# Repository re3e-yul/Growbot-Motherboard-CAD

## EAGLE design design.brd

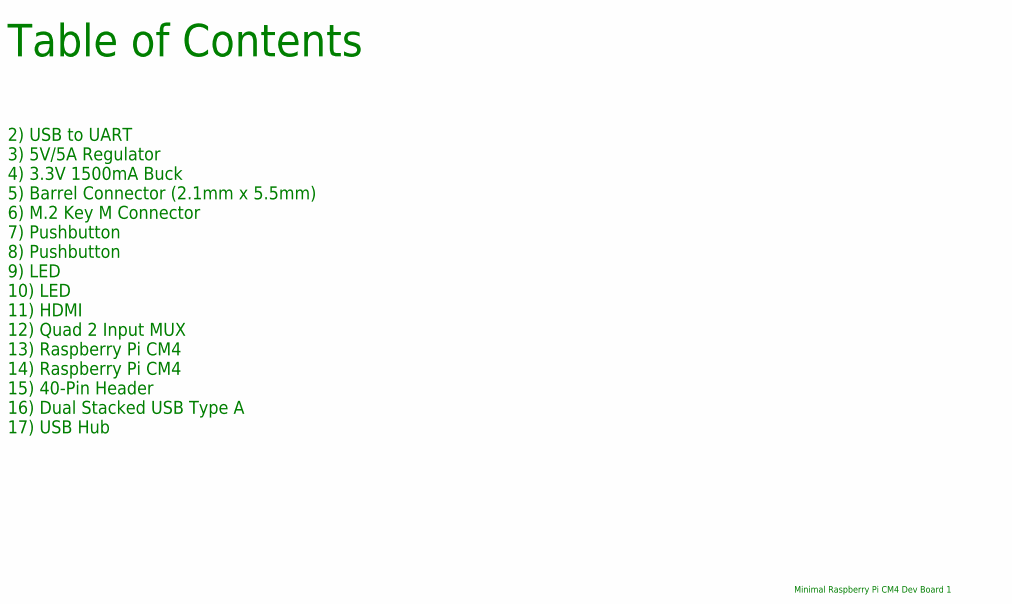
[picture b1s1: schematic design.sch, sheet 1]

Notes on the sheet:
Table of Contents
Minimal Raspberry Pi CM4 Dev Board 1
2) USB to UART
3) 5V/5A Regulator
4) 3.3V 1500mA Buck
5) Barrel Connector (2.1mm x 5.5mm)
6) M.2 Key M Connector
7) Pushbutton
8) Pushbutton
9) LED
10) LED
11) HDMI
12) Quad 2 Input MUX
13) Raspberry Pi CM4
14) Raspberry Pi CM4
15) 40-Pin Header
16) Dual Stacked USB Type A
17) USB Hub

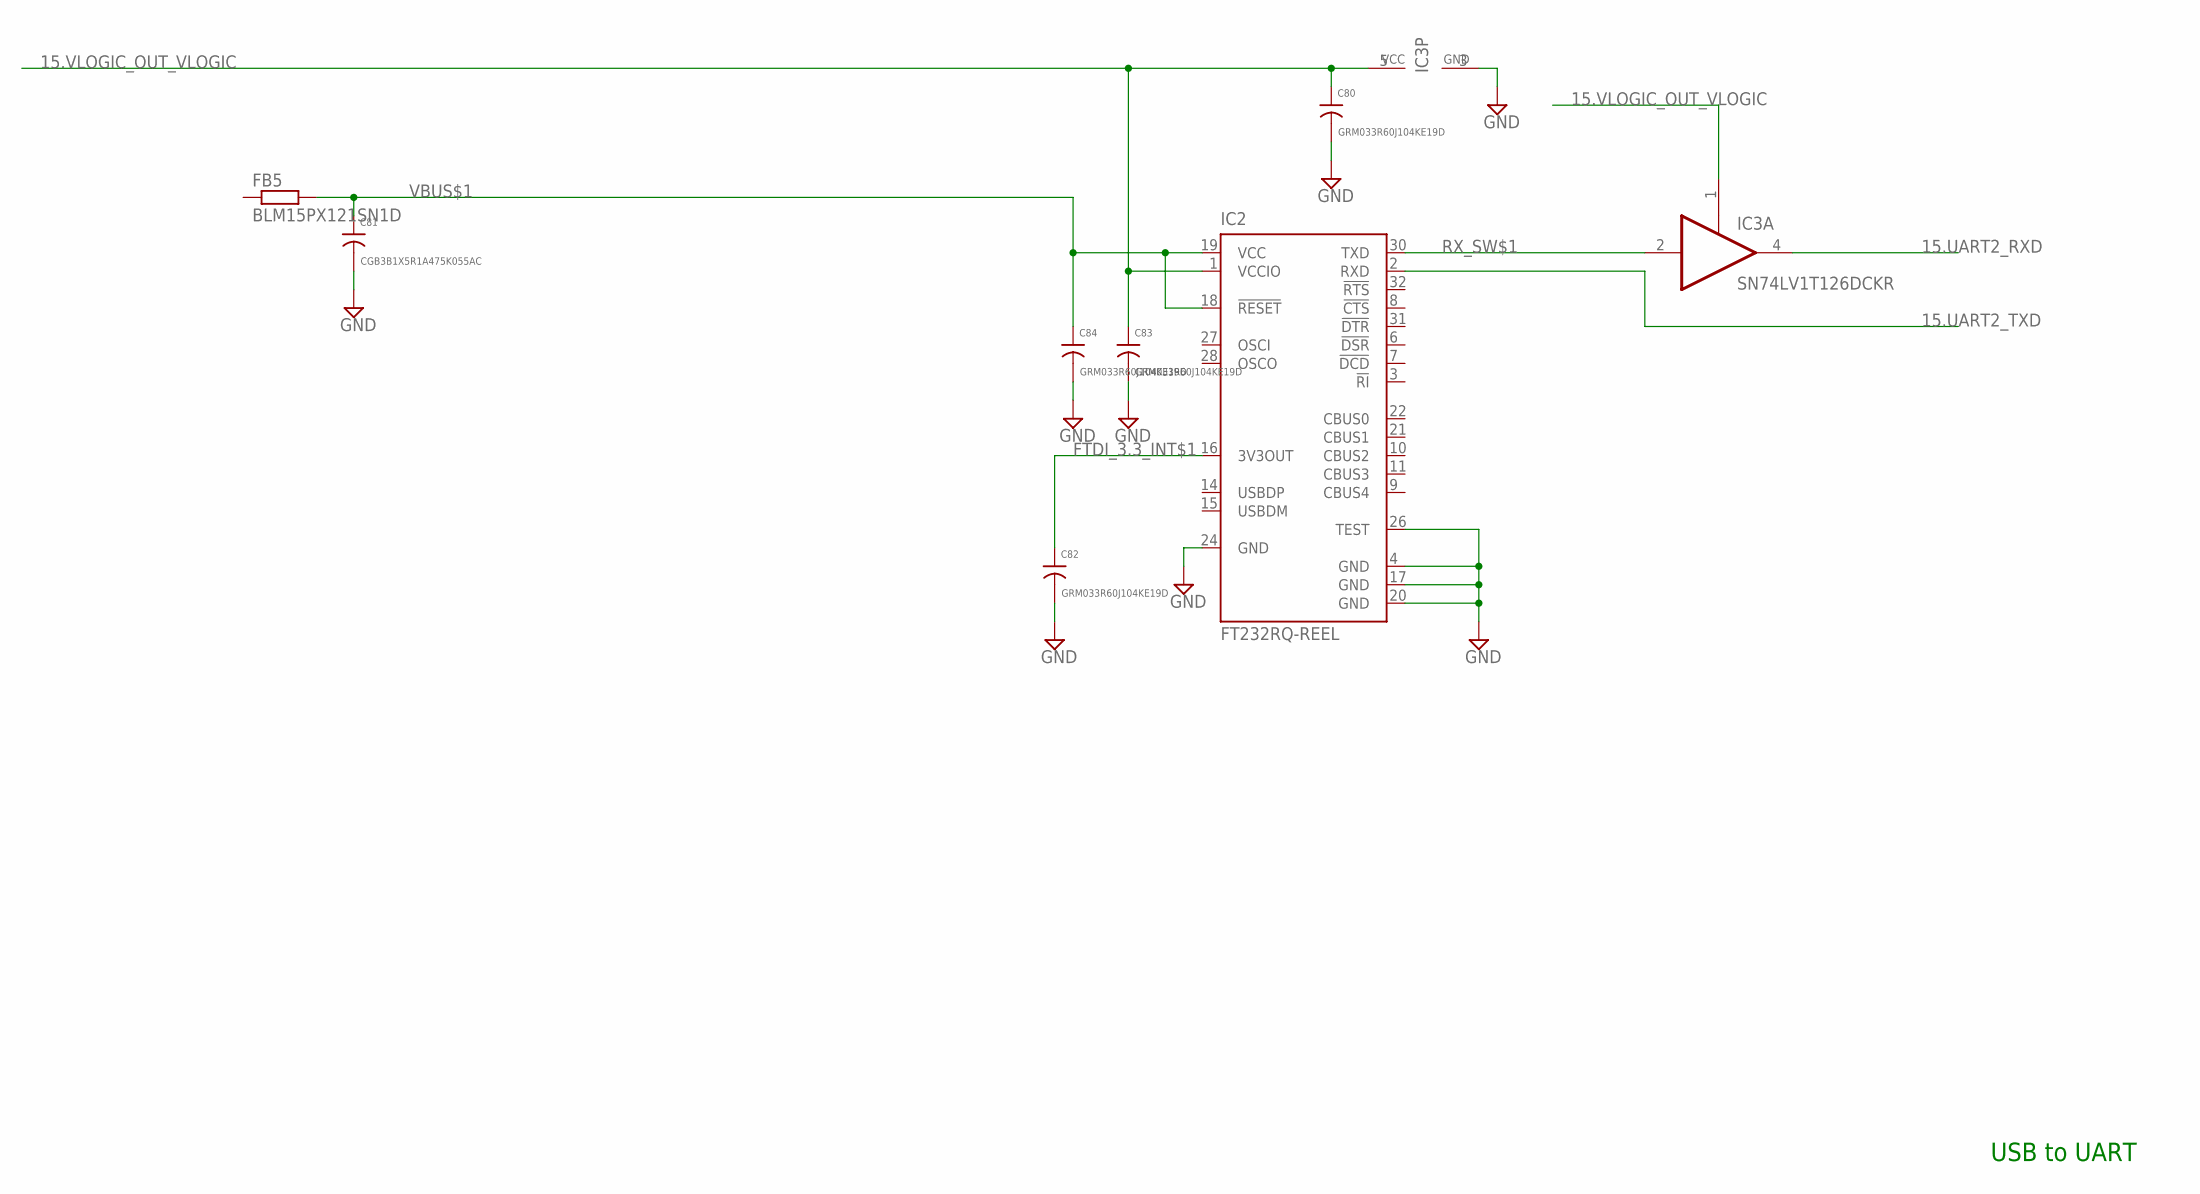
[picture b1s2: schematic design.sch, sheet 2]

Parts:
C80, C82, C83, C84: GRM033R60J104KE19D; 0201
C81: CGB3B1X5R1A475K055AC; 0603
FB5: BLM15PX121SN1D; 0402
IC2: FT232RQ-REEL; QFN32
IC3: SN74LV1T126DCKR; SC70-5

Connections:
15.UART2_RXD: IC3.4 (O); also elsewhere on the board
15.UART2_TXD: IC2.2 (RXD); also elsewhere on the board
15.VLOGIC_OUT_VLOGIC: C80.1, C83.1, IC2.1 (VCCIO), IC3.1 (OE), IC3.5 (VCC); also elsewhere on the board
FTDI_3.3_INT$1: C82.1, IC2.16 (3V3OUT)
GND: C80.2, C81.2, C82.2, C83.2, C84.2, IC2.4 (GND), IC2.17 (GND), IC2.20 (GND), IC2.24 (GND), IC2.26 (TEST), IC3.3 (GND); also elsewhere on the board
RX_SW$1: IC2.30 (TXD), IC3.2 (I)
VBUS$1: C81.1, C84.1, FB5.2, IC2.18 (!RESET), IC2.19 (VCC)

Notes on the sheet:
USB to UART

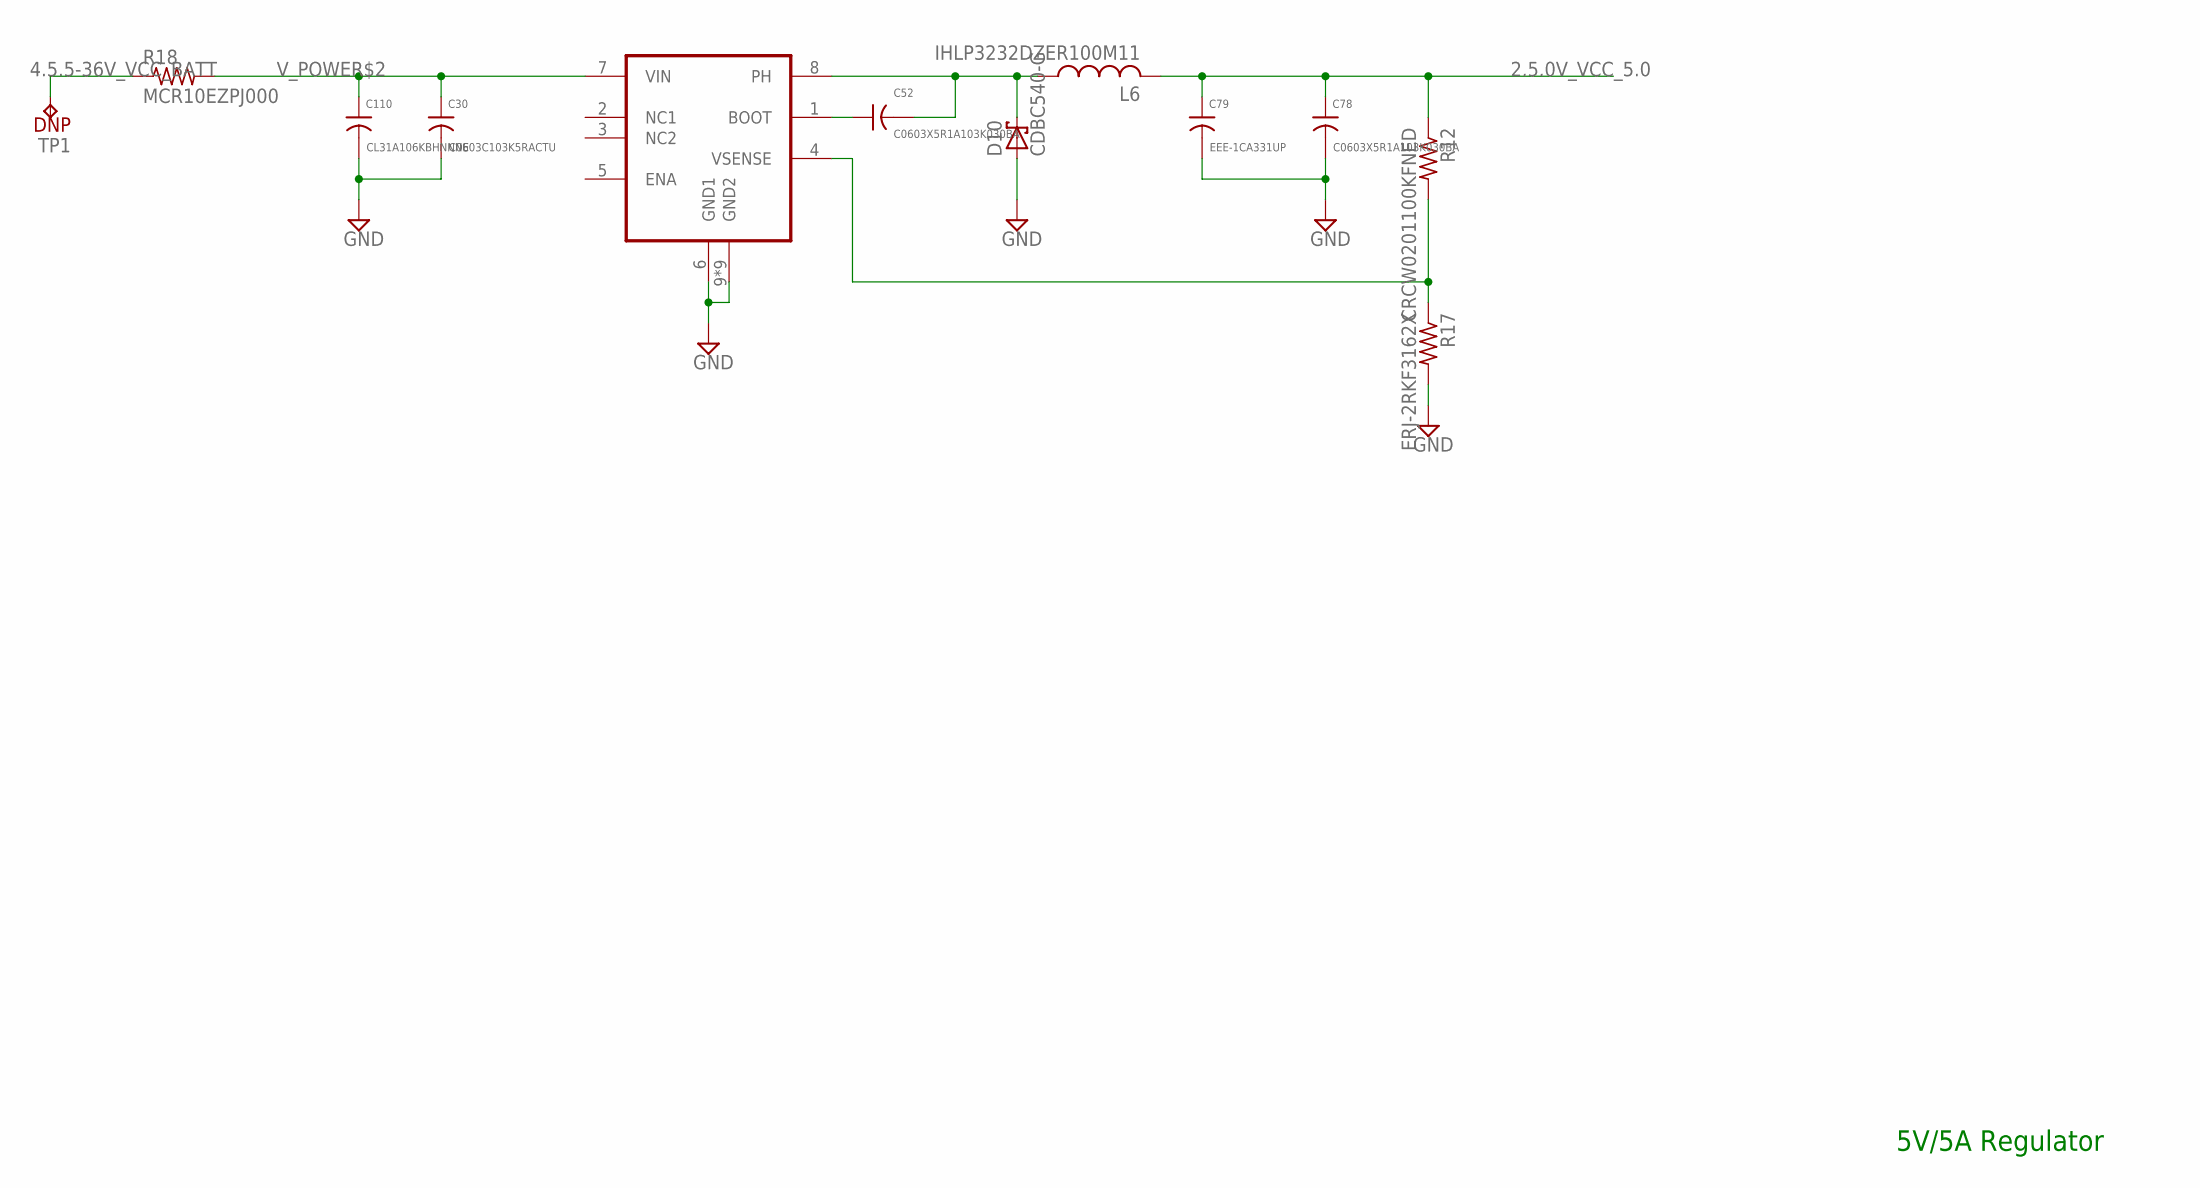
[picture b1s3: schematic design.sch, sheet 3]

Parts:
C30: C0603C103K5RACTU; 0603
C52, C78: C0603X5R1A103K030BA; 0201
C79: EEE-1CA331UP; PANASONIC_F
C110: CL31A106KBHNNNE; 1206
D10: CDBC540-G; DO-214AB
L6: IHLP3232DZER100M11; 3232DZ
R12: CRCW0201100KFNED; 0201
R17: ERJ-2RKF3162X; 0402
R18: MCR10EZPJ000; 0805
TP1: DNP; TP0500
U6: TPS5450QDDARQ1; 8SO_POWERPAD

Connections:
2.5.0V_VCC_5.0: C78.1, C79.+ (1), L6.2, R12.1; also elsewhere on the board
4.5.5-36V_VCC_BATT: R18.1, TP1.1; also elsewhere on the board
BOOT$2: C52.1, U6.1 (BOOT)
GND: C30.2, C78.2, C79.- (2), C110.2, D10.A, R17.2, U6.6 (GND1), U6.9 (GND2), U6.PWRPAD1 (GND2), U6.PWRPAD2 (GND2), U6.PWRPAD3 (GND2), U6.PWRPAD4 (GND2), U6.PWRPAD5 (GND2), U6.PWRPAD6 (GND2), U6.PWRPAD7 (GND2), U6.PWRPAD8 (GND2); also elsewhere on the board
PH$2: C52.2, D10.C, L6.1, U6.8 (PH)
VSENSE$2: R12.2, R17.1, U6.4 (VSENSE)
V_POWER$2: C30.1, C110.1, R18.2, U6.7 (VIN)

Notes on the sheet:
5V/5A Regulator

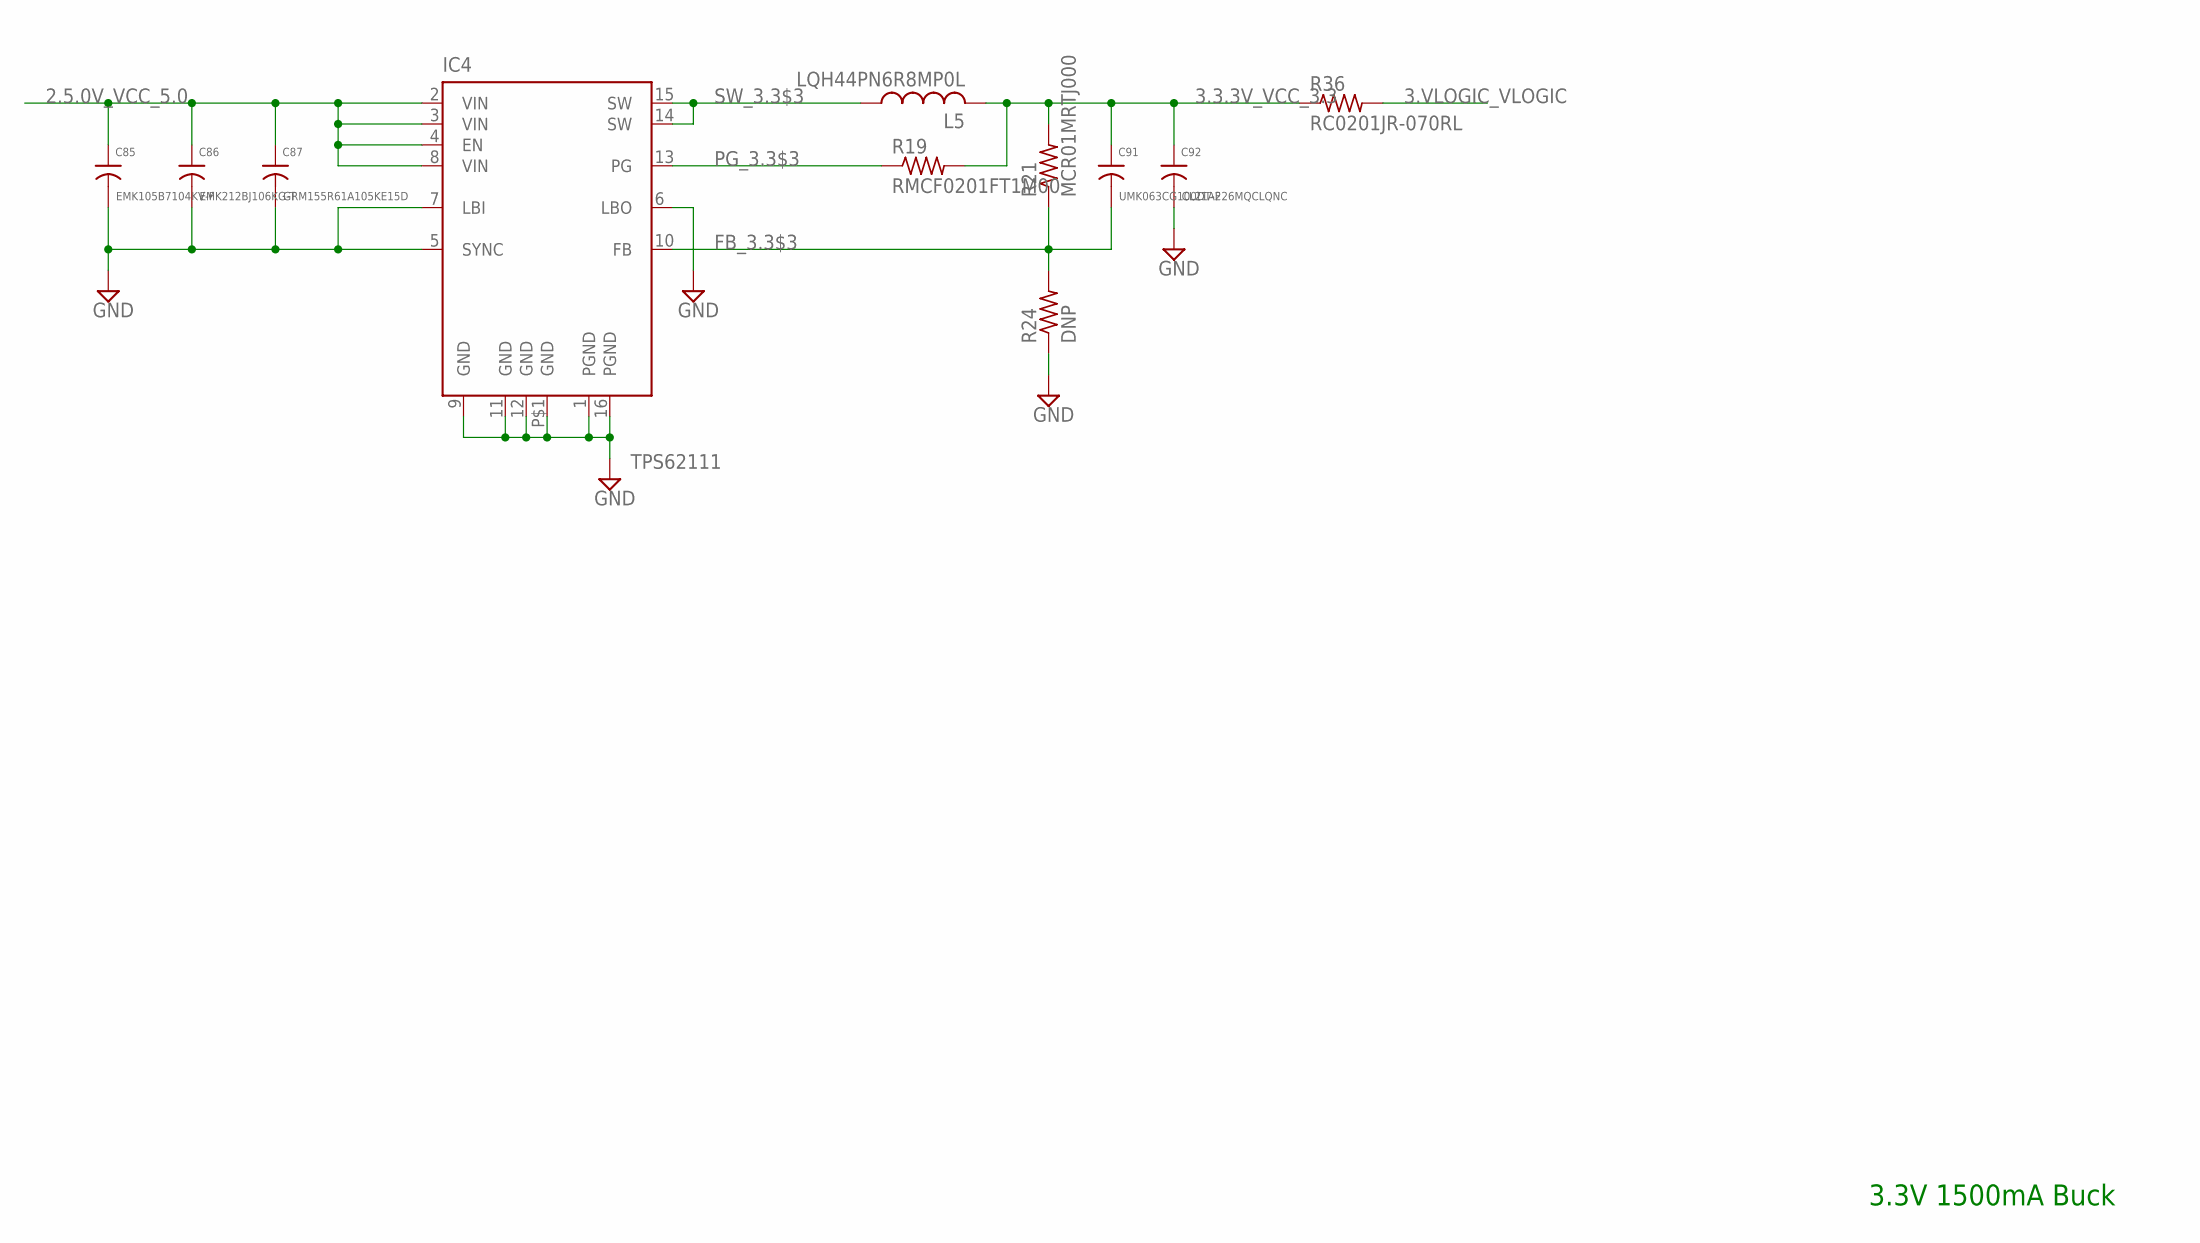
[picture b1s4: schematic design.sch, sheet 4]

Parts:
C85: EMK105B7104KV-F; 0402
C86: EMK212BJ106KG-T; 0805
C87: GRM155R61A105KE15D; 0402
C91: UMK063CG100DT-F; 0201
C92: CL21A226MQCLQNC; 0805
IC4: TPS62111; PQFP16
L5: LQH44PN6R8MP0L; 1515
R19: RMCF0201FT1M00; 0201
R21: MCR01MRTJ000; 0402
R24: DNP; 0402
R36: RC0201JR-070RL; 0201

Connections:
2.5.0V_VCC_5.0: C85.1, C86.1, C87.1, IC4.2 (VIN), IC4.3 (VIN), IC4.4 (EN), IC4.8 (VIN); also elsewhere on the board
3.3.3V_VCC_3.3: C91.1, C92.1, L5.2, R19.2, R21.2, R36.1; also elsewhere on the board
3.VLOGIC_VLOGIC: R36.2
FB_3.3$3: C91.2, IC4.10 (FB), R21.1, R24.2
GND: C85.2, C86.2, C87.2, C92.2, IC4.1 (PGND), IC4.5 (SYNC), IC4.6 (LBO), IC4.7 (LBI), IC4.9 (GND), IC4.11 (GND), IC4.12 (GND), IC4.16 (PGND), IC4.P$1 (GND), R24.1; also elsewhere on the board
PG_3.3$3: IC4.13 (PG), R19.1
SW_3.3$3: IC4.14 (SW), IC4.15 (SW), L5.1

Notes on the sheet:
3.3V 1500mA Buck

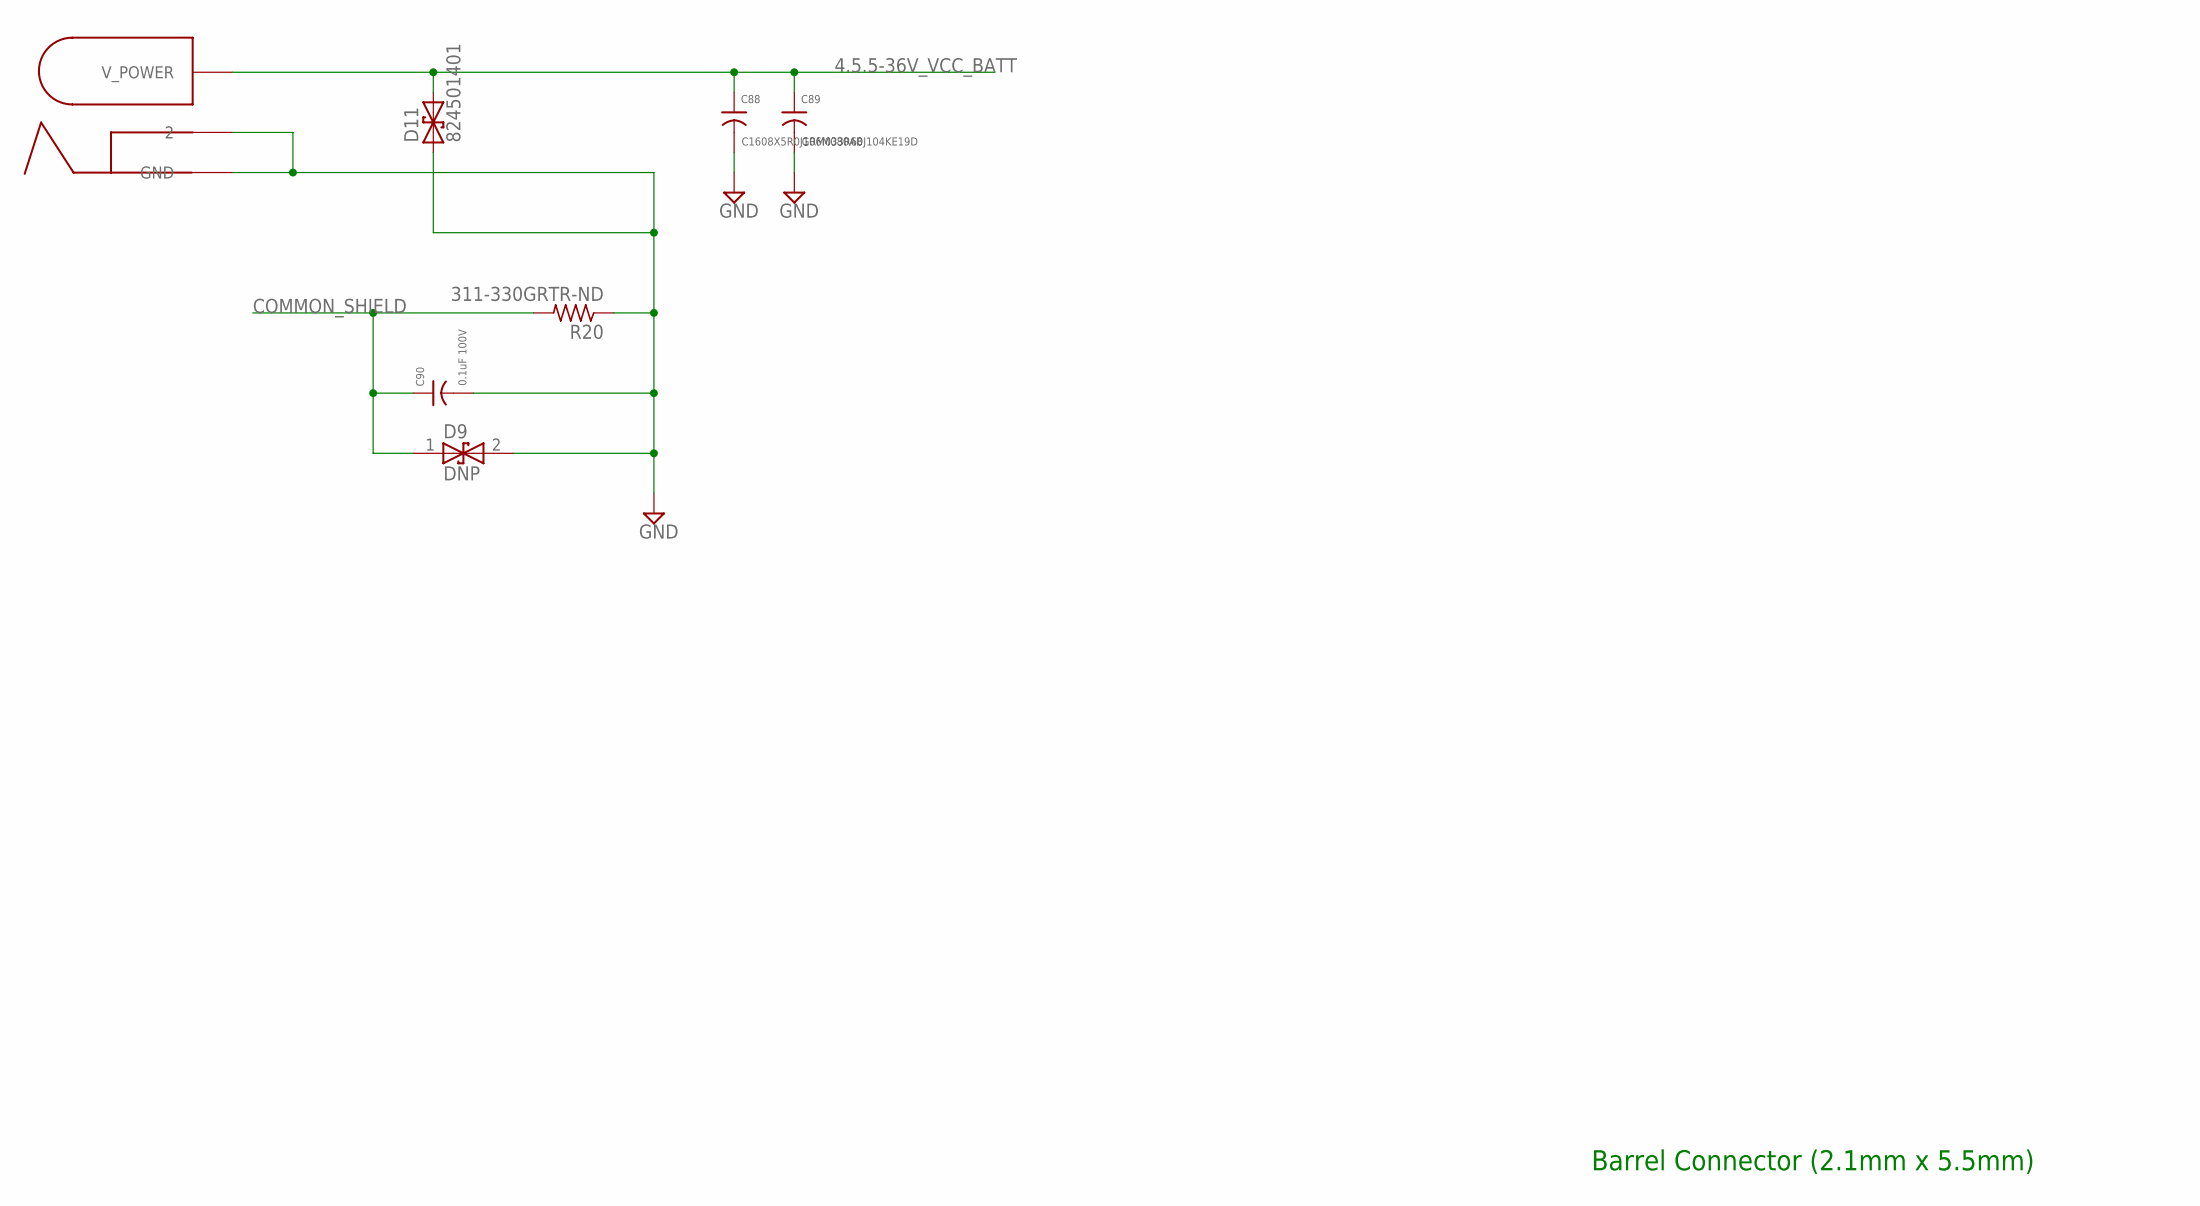
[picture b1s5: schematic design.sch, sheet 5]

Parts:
C88: C1608X5R0J106M080AB; 0603
C89: GRM033R60J104KE19D; 0201
C90: 0.1uF 100V; 1206
D9: DNP; TPD1E
D11: 824501401; SMAJ
J3: PJ-002AH; PJ-002A
R20: 311-330GRTR-ND; 0603

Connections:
4.5.5-36V_VCC_BATT: C88.1, C89.1, D11.C (2), J3.1 (V_POWER); also elsewhere on the board
COMMON_SHIELD: C90.1, D9.1, R20.2; also elsewhere on the board
GND: C88.2, C89.2, C90.2, D9.2, D11.A (1), J3.2 (GND), J3.3 (2), R20.1; also elsewhere on the board

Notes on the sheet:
Barrel Connector (2.1mm x 5.5mm)

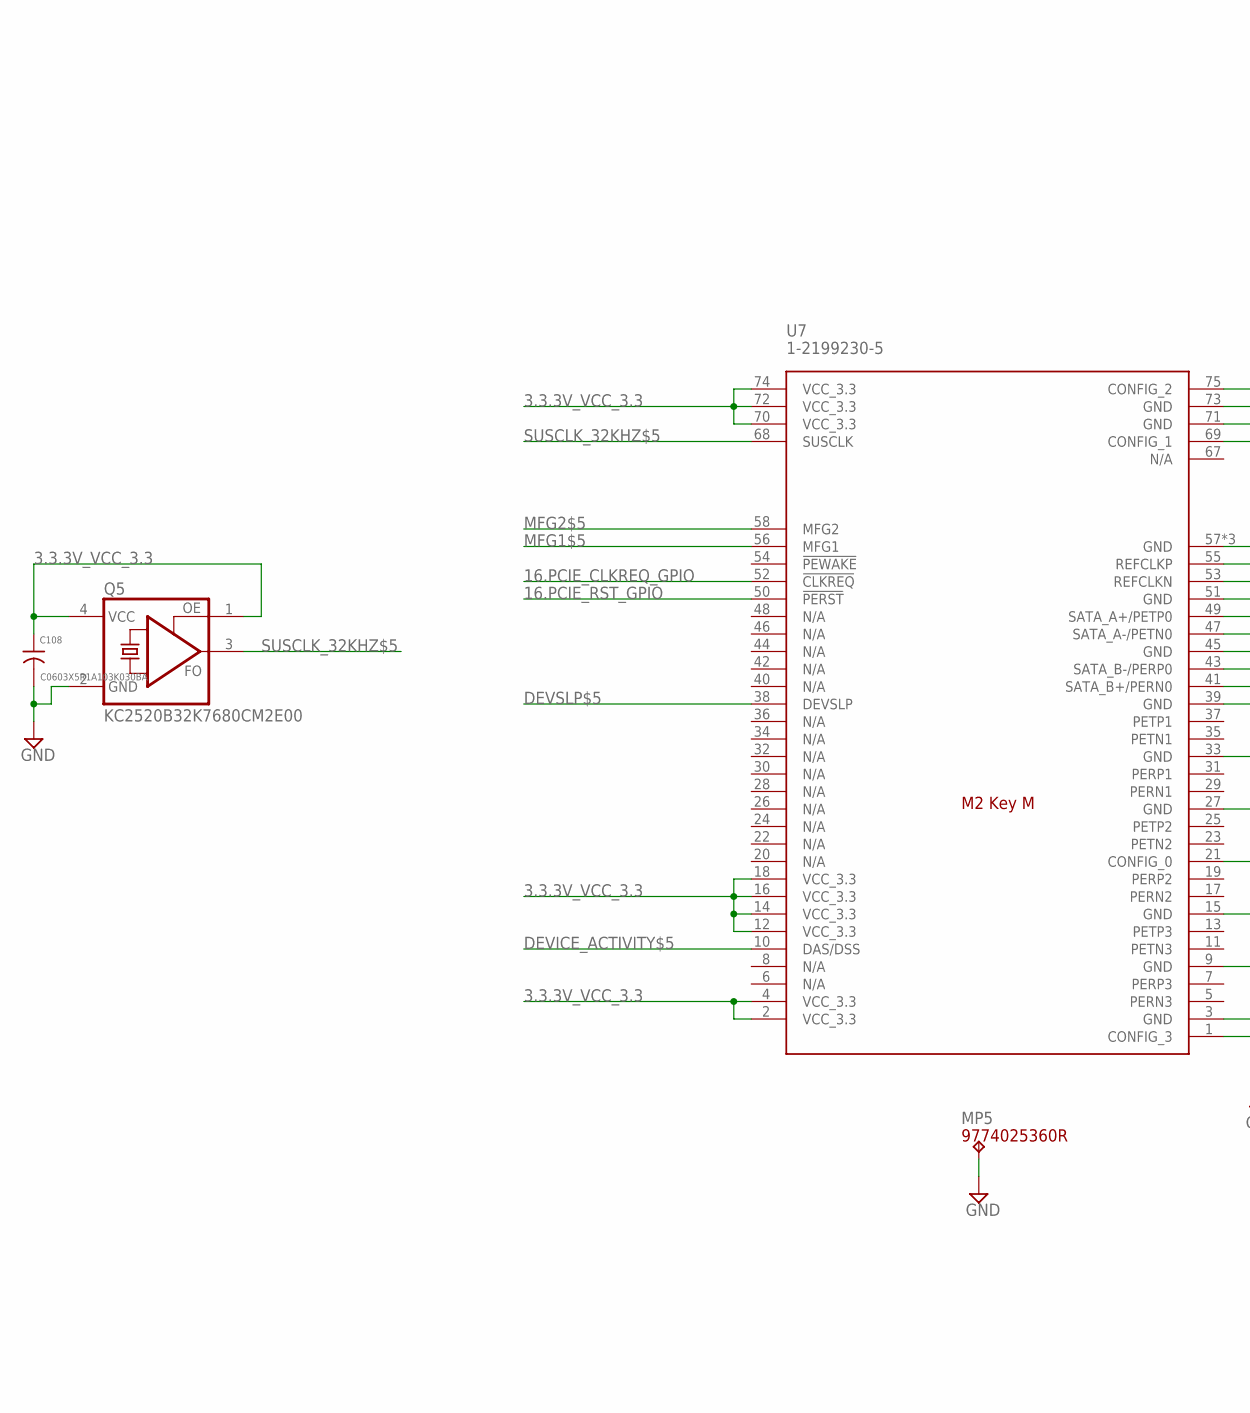
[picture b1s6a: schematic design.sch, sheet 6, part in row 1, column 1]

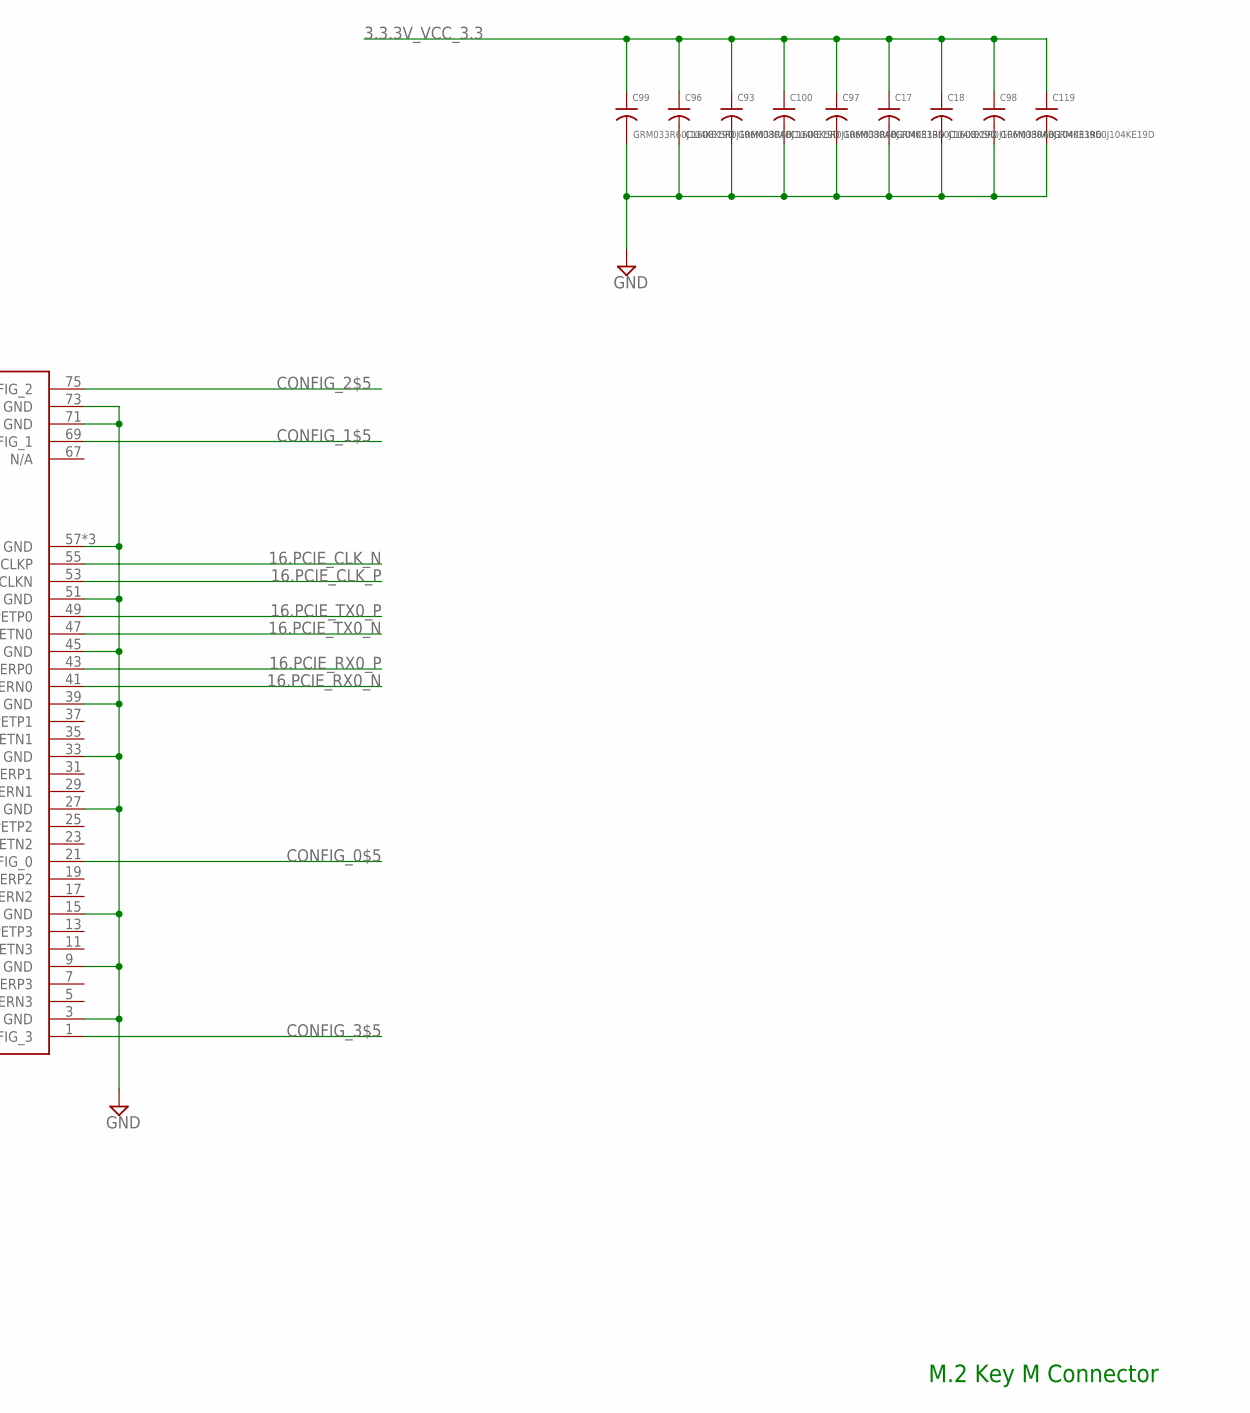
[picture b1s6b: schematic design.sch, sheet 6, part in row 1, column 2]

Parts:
C17, C93, C97, C98, C99, C119: GRM033R60J104KE19D; 0201
C18, C96, C100: C1608X5R0J106M080AB; 0603
C108: C0603X5R1A103K030BA; 0201
MP5: 9774025360R; WA-SMSI_9774___360
Q5: KC2520B32K7680CM2E00; VLGA-4
U7: 1-2199230-5; 2199230_KEY_M

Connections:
3.3.3V_VCC_3.3: C17.1, C18.1, C93.1, C96.1, C97.1, C98.1, C99.1, C100.1, C108.1, C119.1, Q5.1 (OE), Q5.4 (VCC), U7.2 (VCC_3.3), U7.4 (VCC_3.3), U7.12 (VCC_3.3), U7.14 (VCC_3.3), U7.16 (VCC_3.3), U7.18 (VCC_3.3), U7.70 (VCC_3.3), U7.72 (VCC_3.3), U7.74 (VCC_3.3); also elsewhere on the board
16.PCIE_CLKREQ_GPIO: U7.52 (!CLKREQ); also elsewhere on the board
16.PCIE_CLK_N: U7.55 (REFCLKP); also elsewhere on the board
16.PCIE_CLK_P: U7.53 (REFCLKN); also elsewhere on the board
16.PCIE_RST_GPIO: U7.50 (!PERST); also elsewhere on the board
16.PCIE_RX0_N: U7.41 (SATA_B+/PERN0); also elsewhere on the board
16.PCIE_RX0_P: U7.43 (SATA_B-/PERP0); also elsewhere on the board
16.PCIE_TX0_N: U7.47 (SATA_A-/PETN0); also elsewhere on the board
16.PCIE_TX0_P: U7.49 (SATA_A+/PETP0); also elsewhere on the board
CONFIG_0$5: U7.21 (CONFIG_0)
CONFIG_1$5: U7.69 (CONFIG_1)
CONFIG_2$5: U7.75 (CONFIG_2)
CONFIG_3$5: U7.1 (CONFIG_3)
DEVICE_ACTIVITY$5: U7.10 (DAS/DSS)
DEVSLP$5: U7.38 (DEVSLP)
GND: C17.2, C18.2, C93.2, C96.2, C97.2, C98.2, C99.2, C100.2, C108.2, C119.2, MP5.1, Q5.2 (GND), U7.3 (GND), U7.9 (GND), U7.15 (GND), U7.27 (GND), U7.33 (GND), U7.39 (GND), U7.45 (GND), U7.51 (GND), U7.57 (GND), U7.71 (GND), U7.73 (GND), U7.P$1 (GND), U7.P$2 (GND); also elsewhere on the board
MFG1$5: U7.56 (MFG1)
MFG2$5: U7.58 (MFG2)
SUSCLK_32KHZ$5: Q5.3 (FO), U7.68 (SUSCLK)

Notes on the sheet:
M.2 Key M Connector

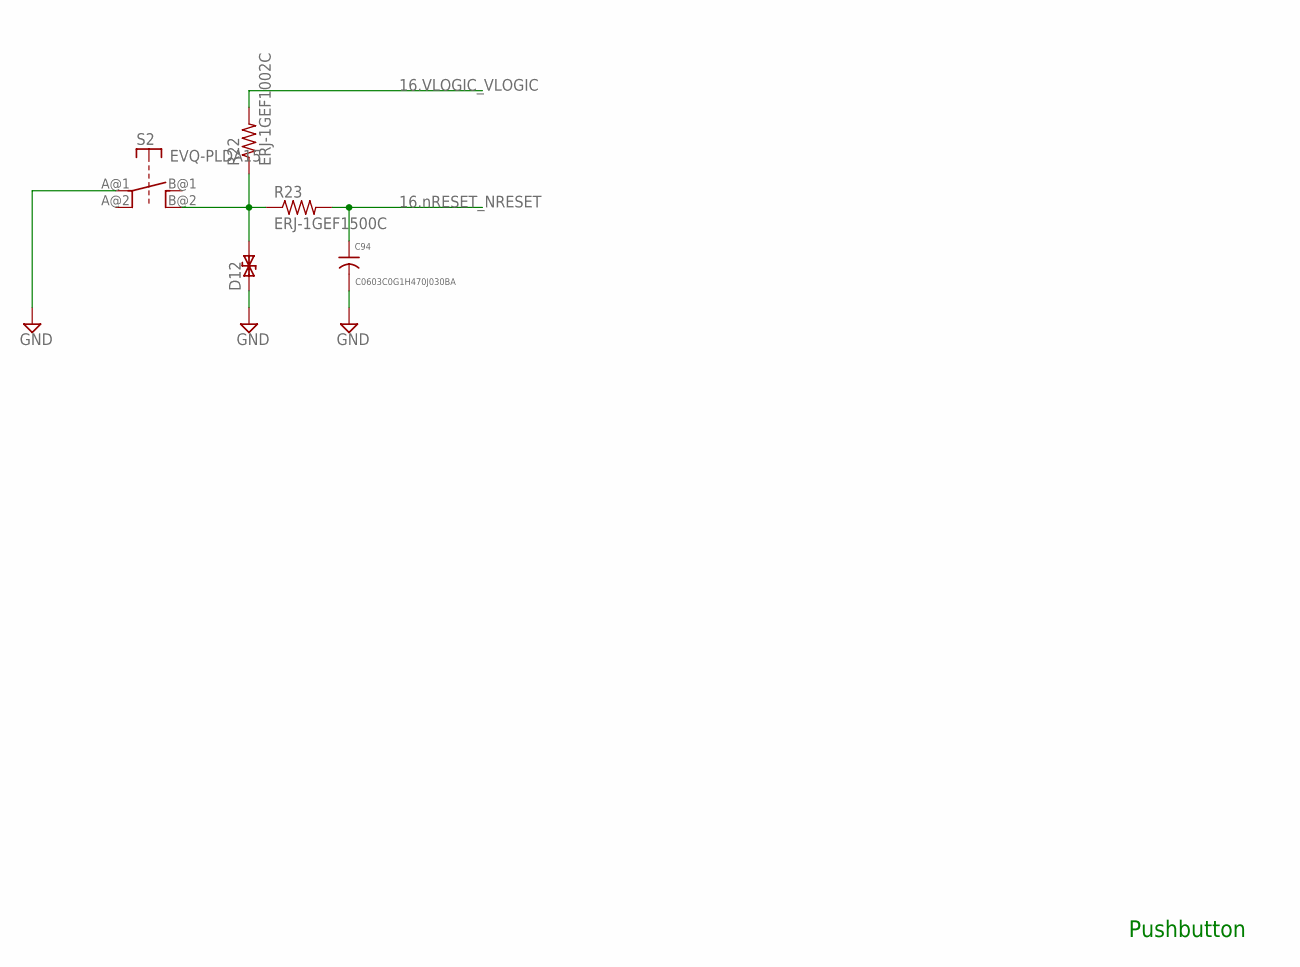
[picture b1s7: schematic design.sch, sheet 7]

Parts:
C94: C0603C0G1H470J030BA; 0201
D12: B72590D0050A060; D0402
R22: ERJ-1GEF1002C; 0201
R23: ERJ-1GEF1500C; 0201
S2: EVQ-PLDA15; EVQ

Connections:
16.VLOGIC_VLOGIC: R22.2; also elsewhere on the board
16.nRESET_NRESET: C94.1, R23.2; also elsewhere on the board
BTN_A$10: D12.P2, R22.1, R23.1, S2.B@2 (B')
GND: C94.2, D12.P1, S2.A@1 (A); also elsewhere on the board

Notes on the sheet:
Pushbutton

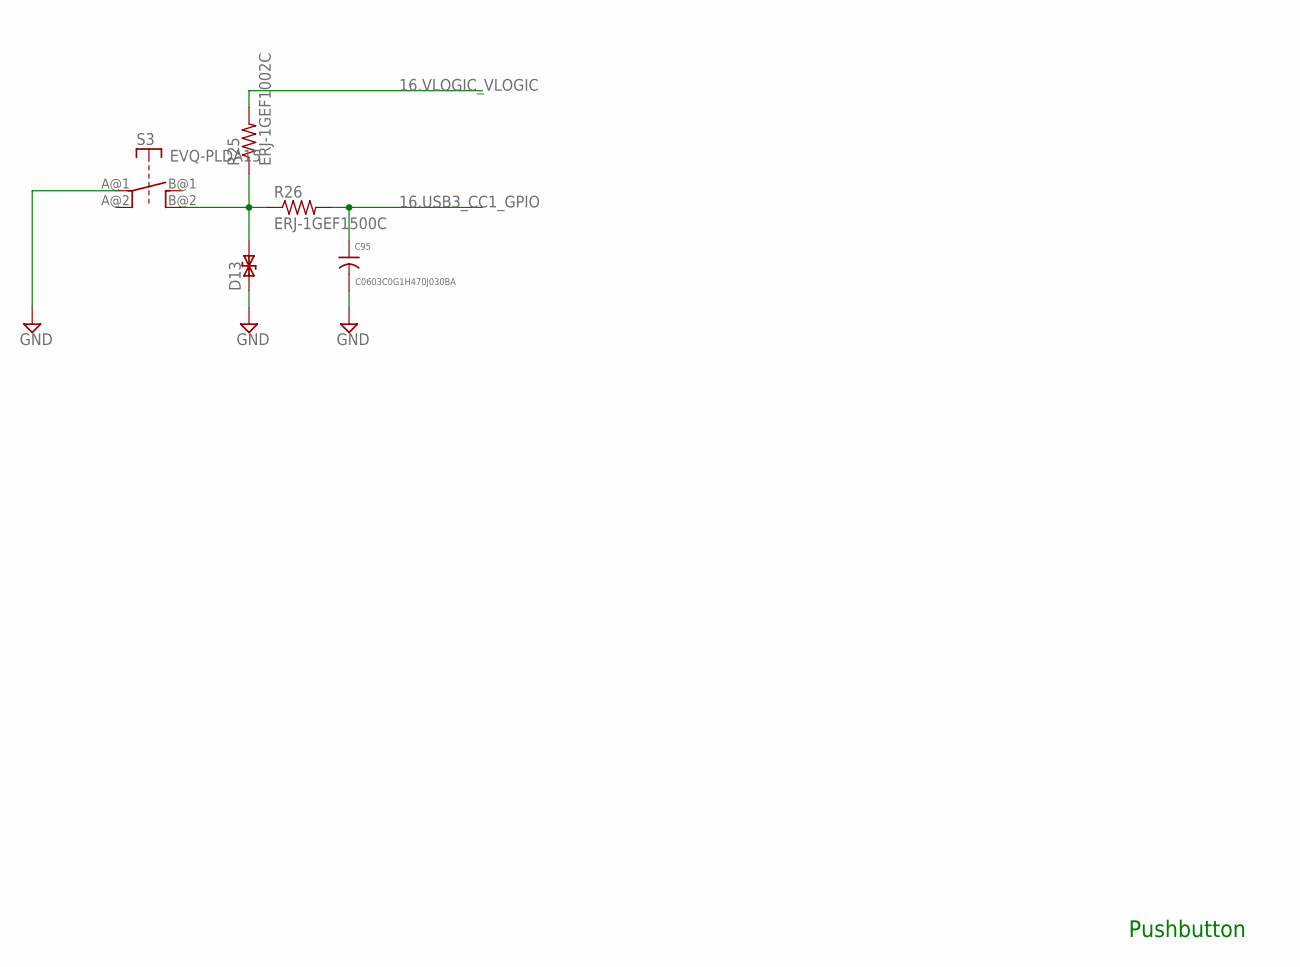
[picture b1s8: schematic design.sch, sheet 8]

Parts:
C95: C0603C0G1H470J030BA; 0201
D13: B72590D0050A060; D0402
R25: ERJ-1GEF1002C; 0201
R26: ERJ-1GEF1500C; 0201
S3: EVQ-PLDA15; EVQ

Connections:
16.USB3_CC1_GPIO: C95.1, R26.2; also elsewhere on the board
16.VLOGIC_VLOGIC: R25.2; also elsewhere on the board
BTN_A$11: D13.P2, R25.1, R26.1, S3.B@2 (B')
GND: C95.2, D13.P1, S3.A@1 (A); also elsewhere on the board

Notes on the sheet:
Pushbutton

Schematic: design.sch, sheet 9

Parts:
D14: 150060RS75000; D0603
Q6: BSS138; SOT23
R27: ERJ-1GNJ102C; 0201
R28: ERJ-2RKF3000X; 0402
R29: CRCW0201100KFNED; 0201

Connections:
3.3.3V_VCC_3.3: R28.2; also elsewhere on the board
16.GPIO23_GPIO: R27.1, R29.2; also elsewhere on the board
ANODE$12: D14.A, R28.1
GATE$12: Q6.1 (G), R27.2
GND: Q6.2 (S), R29.1; also elsewhere on the board
LED-$12: D14.C, Q6.3 (D)

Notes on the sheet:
LED

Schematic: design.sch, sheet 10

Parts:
D8: 150060GS75000; D0603
Q4: BSS138; SOT23
R30: CRCW0201100KFNED; 0201
R31: ERJ-2RKF3000X; 0402
R35: ERJ-1GNJ102C; 0201

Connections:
3.3.3V_VCC_3.3: R31.2; also elsewhere on the board
16.SYS_EN_SYSEN: R30.2, R35.1; also elsewhere on the board
ANODE$13: D8.A, R31.1
GATE$13: Q4.1 (G), R35.2
GND: Q4.2 (S), R30.1; also elsewhere on the board
LED-$13: D8.C, Q4.3 (D)

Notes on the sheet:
LED

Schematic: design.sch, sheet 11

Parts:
C101, C102, C106, C107, C111: GRM033R60J104KE19D; 0201
C103, C104: C0603X5R1A103K030BA; 0201
L1, L2, L7, L8: 7442335900; 0504-DLP11S
R32: CRCW040275R0FKED; 0402
RP3: DNP; 741X08
U3: 685119134923; 47151-001
U5: TPD13S523PWR; TSSOP16
U$26: TXS0104ERGYR; S-PVQFN-N14

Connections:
2.5.0V_VCC_5.0: C106.1, C107.1, U5.5 (5V_SUPPLY), U$26.14 (VCCB); also elsewhere on the board
16.HDMI0_CEC: RP3.4, U$26.2 (A1); also elsewhere on the board
16.HDMI0_CLOCK_N: L8.2, U5.9 (D3-); also elsewhere on the board
16.HDMI0_CLOCK_P: L8.3, U5.10 (D3+); also elsewhere on the board
16.HDMI0_D0_N: L7.2, U5.11 (D2-); also elsewhere on the board
16.HDMI0_D0_P: L7.3, U5.12 (D2+); also elsewhere on the board
16.HDMI0_D1_N: L2.2, U5.13 (D1-); also elsewhere on the board
16.HDMI0_D1_P: L2.3, U5.14 (D1+); also elsewhere on the board
16.HDMI0_D2_N: L1.2, U5.15 (D0-); also elsewhere on the board
16.HDMI0_D2_P: L1.3, U5.16 (D0+); also elsewhere on the board
16.HDMI0_DDC_SCL: RP3.3, U$26.3 (A2); also elsewhere on the board
16.HDMI0_DDC_SDA: RP3.2, U$26.4 (A3); also elsewhere on the board
16.HDMI0_HPD: RP3.1, U$26.5 (A4); also elsewhere on the board
16.VLOGIC_VLOGIC: C102.1, C103.1, C104.1, C111.1, U$26.1 (VCCA), U$26.8 (OE); also elsewhere on the board
CEC$14: RP3.5, U3.13, U5.1 (CTRL1), U$26.13 (B1)
COMMON_SHIELD: U3.G1 (20), U3.G2 (21), U3.G3 (22), U3.G4 (23); also elsewhere on the board
CON_5V0$14: C101.1, U3.18, U5.6 (5V_OUT)
DDC_SCL$14: RP3.6, U3.15, U5.2 (CTRL2), U$26.12 (B2)
DDC_SDA$14: RP3.7, U3.16, U5.3 (CTRL3), U$26.11 (B3)
GND: C101.2, C102.2, C103.2, C104.2, C106.2, C107.2, C111.2, R32.1, U3.2, U3.5, U3.8, U3.11, U3.17, U5.8 (GND), U$26.7 (GND); also elsewhere on the board
HPD$14: RP3.8, U3.19, U5.4 (CTRL4), U$26.10 (B4)
TXD0_CONN_N$14: L7.1, U3.9
TXD0_CONN_P$14: L7.4, U3.7
TXD1_CONN_N$14: L2.1, U3.6
TXD1_CONN_P$14: L2.4, U3.4
TXD2_CONN_N$14: L1.1, U3.3
TXD2_CONN_P$14: L1.4, U3.1
TXDC_CONN_N$14: L8.1, U3.12
TXDC_CONN_P$14: L8.4, U3.10
UTIL$14: R32.2, U3.14, U5.7 (CTRL5)

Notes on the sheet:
HDMI
PWR<->GND via stitching around bottom side signals (per Toradex layout guidelines)
TPD13S523 sheet says to GND unused pins with 75ohm resistor.
